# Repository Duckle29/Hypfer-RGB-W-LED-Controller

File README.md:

# Hypfer-RGB-W-LED-Controller
An LED controller for controlling a 12v RGB LED strip and white 12v strip. Uses an arduino and an nRF24l01+

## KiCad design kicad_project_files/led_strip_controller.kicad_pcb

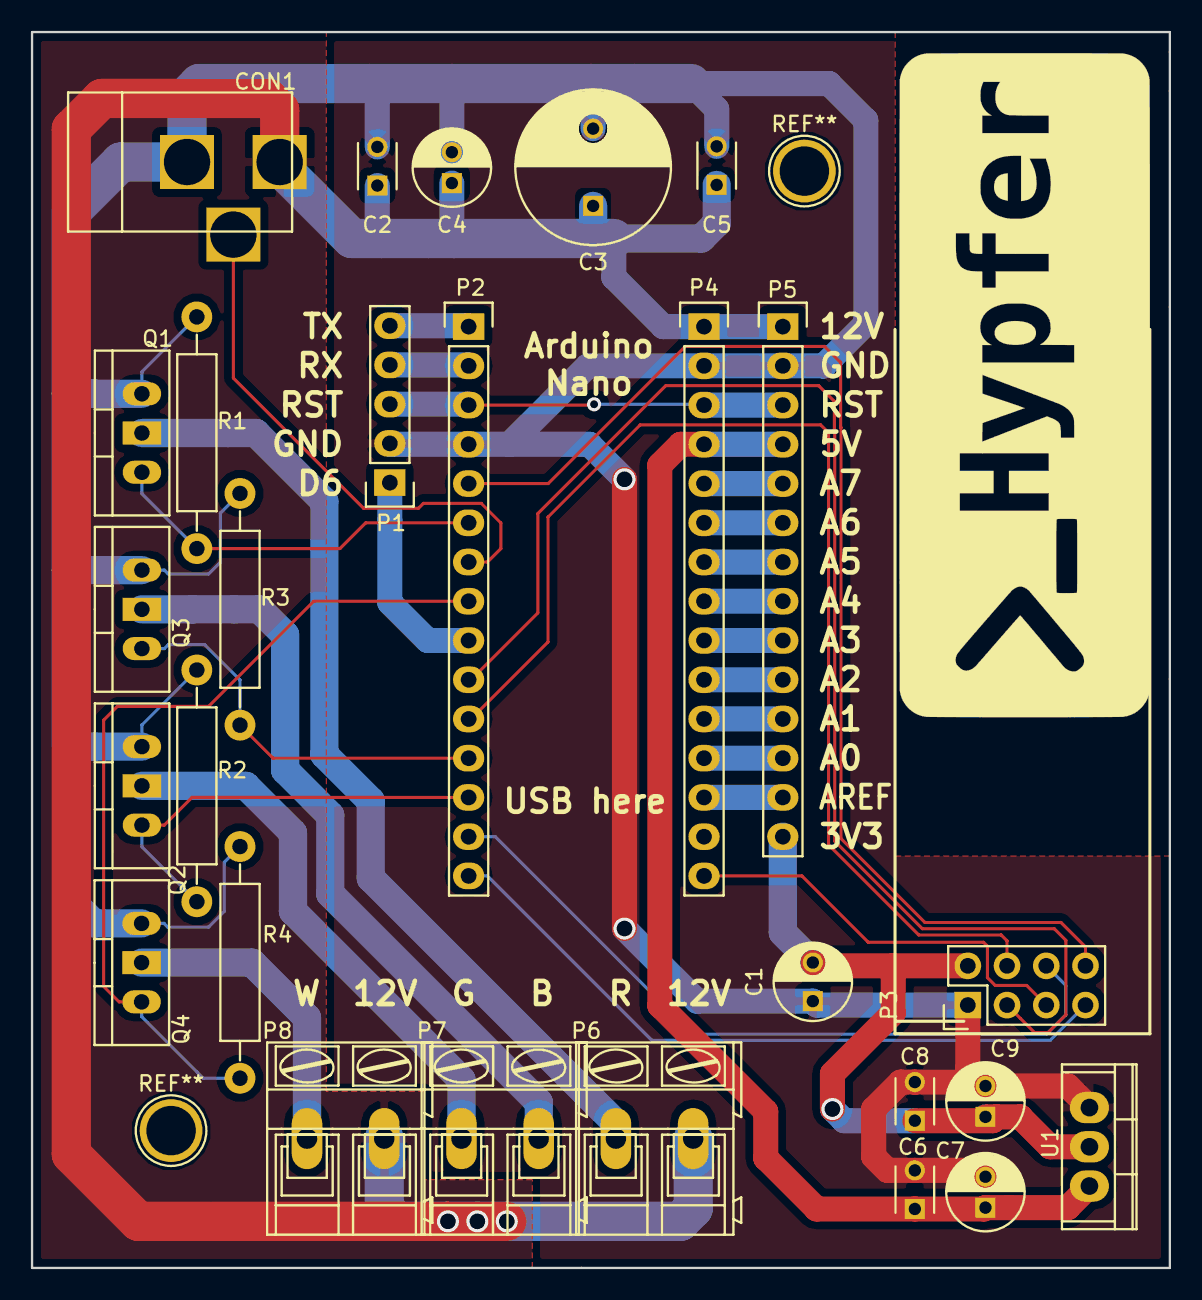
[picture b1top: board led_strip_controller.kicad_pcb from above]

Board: 2 copper layers, 73.7 x 80.0 mm, 27 parts (0 on the bottom side), 32 nets.

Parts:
C1: 1uF; C_Radial_D5_L11_P2.5
C2, C5, C6, C8: 100nF; C_Disc_D3_P2.5
C3: 1000uF; C_Radial_D10_L20_P5
C4, C7, C9: 47uF; C_Radial_D5_L11_P2
CON1: BARREL_JACK
P1: CONN_01X05; Socket_Strip_Straight_1x05
P2, P4: CONN_01X15; Socket_Strip_Straight_1x15
P3: CONN_02X04; Pin_Header_Straight_2x04
P5: CONN_01X14; Socket_Strip_Straight_1x14
P6, P7, P8: CONN_01X02; AK300-2
Q1, Q2, Q3, Q4: Q_NMOS_GDS; Diode_TO-220_Dual_CommonCathode_Vertical
R1, R2, R3, R4: 10k; Resistor_Horizontal_RM15mm
U1: AP1117; TO-220

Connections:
+3V3: C1.2, C8.1, C9.1, P3.2, P5.14, U1.2
+5V: C6.1, C7.1, P4.4, P5.4, U1.3
+12V: C2.1, C3.1, C4.1, C5.1, CON1.1, P4.1, P5.1, P6.2, P8.2
/ADC0: P4.12, P5.12
/ADC1: P4.11, P5.11
/ADC2: P4.10, P5.10
/ADC3: P4.9, P5.9
/ADC4: P4.8, P5.8
/ADC5: P4.7, P5.7
/ADC6: P4.6, P5.6
/ADC7: P4.5, P5.5
/AREF: P4.13, P5.13
/D6: P1.1, P2.9
/RESET: P1.3, P2.3, P4.3, P5.3
/RX: P1.4, P2.2
/TX: P1.5, P2.1
FET_B: P2.12, Q3.1, R3.1
FET_G: P2.13, Q2.1, R2.1
FET_R: P2.6, Q1.1, R1.1
FET_W: P2.8, Q4.1, R4.1
GND: C1.1, C2.2, C3.2, C4.2, C5.2, C6.2, C7.2, C8.2, C9.2, CON1.2, P1.2, P2.4, P3.1, P4.2, P5.2, Q1.3, Q2.3, Q3.3, Q4.3, R1.2, R2.2, R3.2, R4.2, U1.1
JACK_SW: CON1.3, P2.7
LED_B: P7.2, Q3.2
LED_G: P7.1, Q2.2
LED_R: P6.1, Q1.2
LED_W: P8.1, Q4.2
MISO: P2.15, P3.7
MOSI: P2.14, P3.6
SCK: P3.5, P4.15
nRF_CE: P2.10, P3.3
nRF_CSN: P2.11, P3.4
nRF_IRQ: P2.5, P3.8

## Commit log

2015-12-11 Initial commit. Rev 0.1
2015-12-11 Added Gerbers for DirtyPCBs
2015-12-11 Actually added Gerbers for DirtyPCBs
2015-12-12 Added 3D renders
